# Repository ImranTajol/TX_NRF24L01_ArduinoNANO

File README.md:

"# TX_NRF24L01_ArduinoNANO" 
## Transmitter PCB

## Transmitter Schematic

## Transmitter PCB

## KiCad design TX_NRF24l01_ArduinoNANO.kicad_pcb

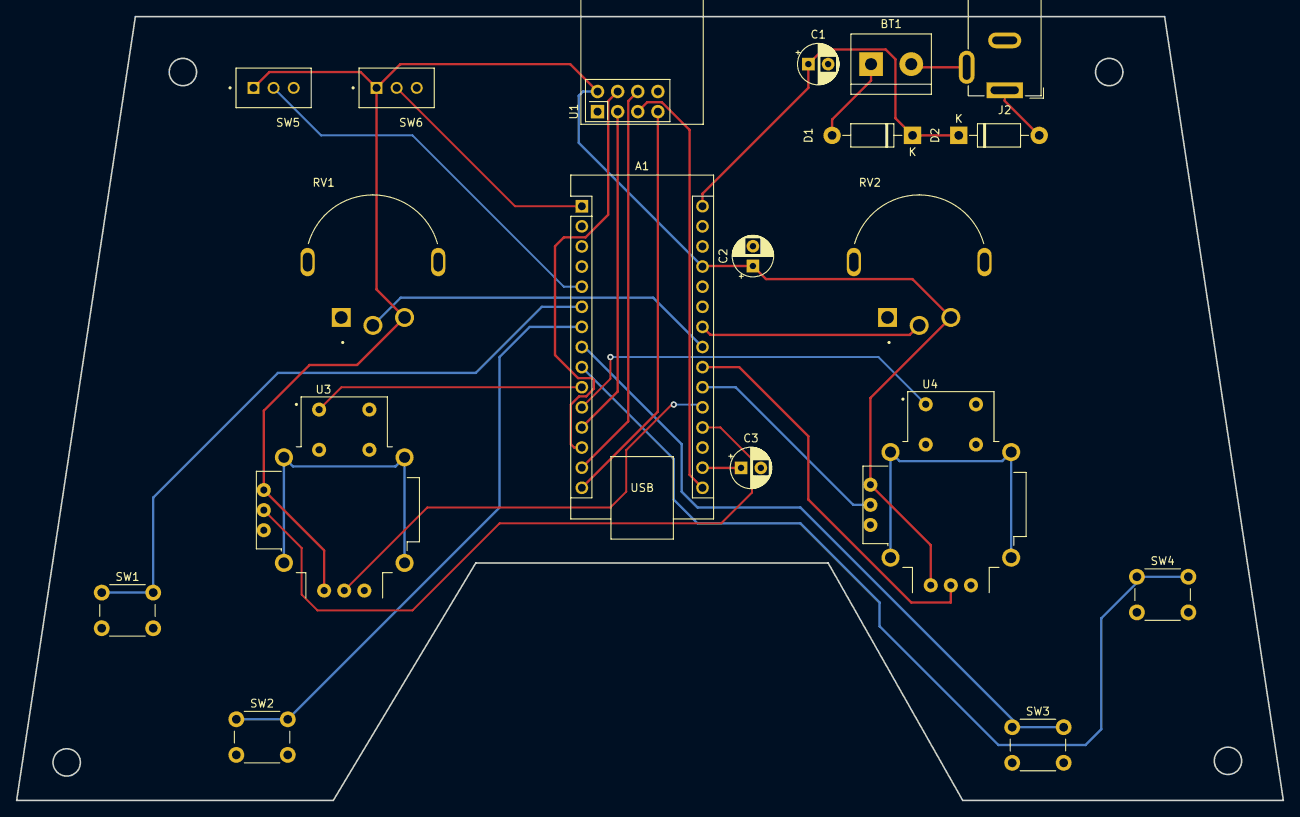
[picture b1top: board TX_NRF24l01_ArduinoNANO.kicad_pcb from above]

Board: 2 copper layers, 160.0 x 99.0 mm, 19 parts (0 on the bottom side), 26 nets.

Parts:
A1: Arduino_Nano_v3.x; Arduino_Nano
BT1: Battery; TerminalBlock_bornier-2_P5.08mm
C1: 10uF; CP_Radial_D5.0mm_P2.50mm
C2, C3: C; CP_Radial_D5.0mm_P2.50mm
D1, D2: 1N4001; D_DO-41_SOD81_P10.16mm_Horizontal
J2: Barrel_Jack_Switch; BarrelJack_GCT_DCJ200-10-A_Horizontal
RV1, RV2: R_Potentiometer; Verticle_Potentiometer
SW1, SW2, SW3, SW4: SW_Push; SW_PUSH_6mm
SW5, SW6: SW_SPDT; SW_ATE1D-2M3-10-Z
U1: NRF24L01_Breakout; nRF24L01_Breakout
U3: Joystick1; Joystick
U4: Joystick2; Joystick

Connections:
+3V3: A1.17 (3V3), C3.1
+5V: A1.27 (+5V), C2.1, RV1.3, RV2.3, SW5.1 (A), SW6.1 (A), U1.2 (VCC), U3.H1 (H+), U3.V1 (V+), U4.H1 (H+), U4.V1 (V+)
Button_1: A1.6 (D3), SW1.1
Button_2: A1.7 (D4), SW2.1
Button_3: A1.8 (D5), SW3.1
Button_4: A1.9 (D6), SW4.1
CE: A1.12 (D9), U1.3 (CE)
CSN: A1.13 (D10), U1.4 (~CSN)
GND: A1.4 (GND), A1.29 (GND), C1.2, C2.2, C3.2, J2.2, RV1.1, RV2.1, SW1.2, SW2.2, SW3.2, SW4.2, SW5.3 (C), SW6.3 (C), U1.1 (GND), U3.B2A (SEL-), U3.H3 (H-), U3.V3 (V-), U4.B2A (SEL-), U4.H3 (H-), U4.V3 (V-)
MISO: A1.15 (D12), U1.7 (MISO)
MOSI: A1.14 (D11), U1.6 (MOSI)
unnamed: BT1.1 (+), D1.2 (A)
unnamed: BT1.2 (-), J2.3
unnamed: D2.2 (A), J2.1
Pot_1_Left: A1.23 (A4), RV1.2
Pot_2_Right: A1.24 (A5), RV2.2
SCK: A1.16 (D13), U1.5 (SCK)
SPDT_1_Left: A1.5 (D2), SW5.2 (B)
SPDT_2_Right: A1.1 (D1/TX), SW6.2 (B)
VIN: A1.30 (VIN), C1.1, D1.1 (K), D2.1 (K)
j1Button: A1.10 (D7), U3.B1A (SEL+)
j1_PotX: A1.19 (A0), U3.V2 (V)
j1_PotY: A1.20 (A1), U3.H2 (H)
j2Button: A1.11 (D8), U4.B1A (SEL+)
j2_PotX: A1.21 (A2), U4.V2 (V)
j2_PotY: A1.22 (A3), U4.H2 (H)

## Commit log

2024-10-30 Add ReadME
2024-10-30 add images
2024-10-30 add images in readme
